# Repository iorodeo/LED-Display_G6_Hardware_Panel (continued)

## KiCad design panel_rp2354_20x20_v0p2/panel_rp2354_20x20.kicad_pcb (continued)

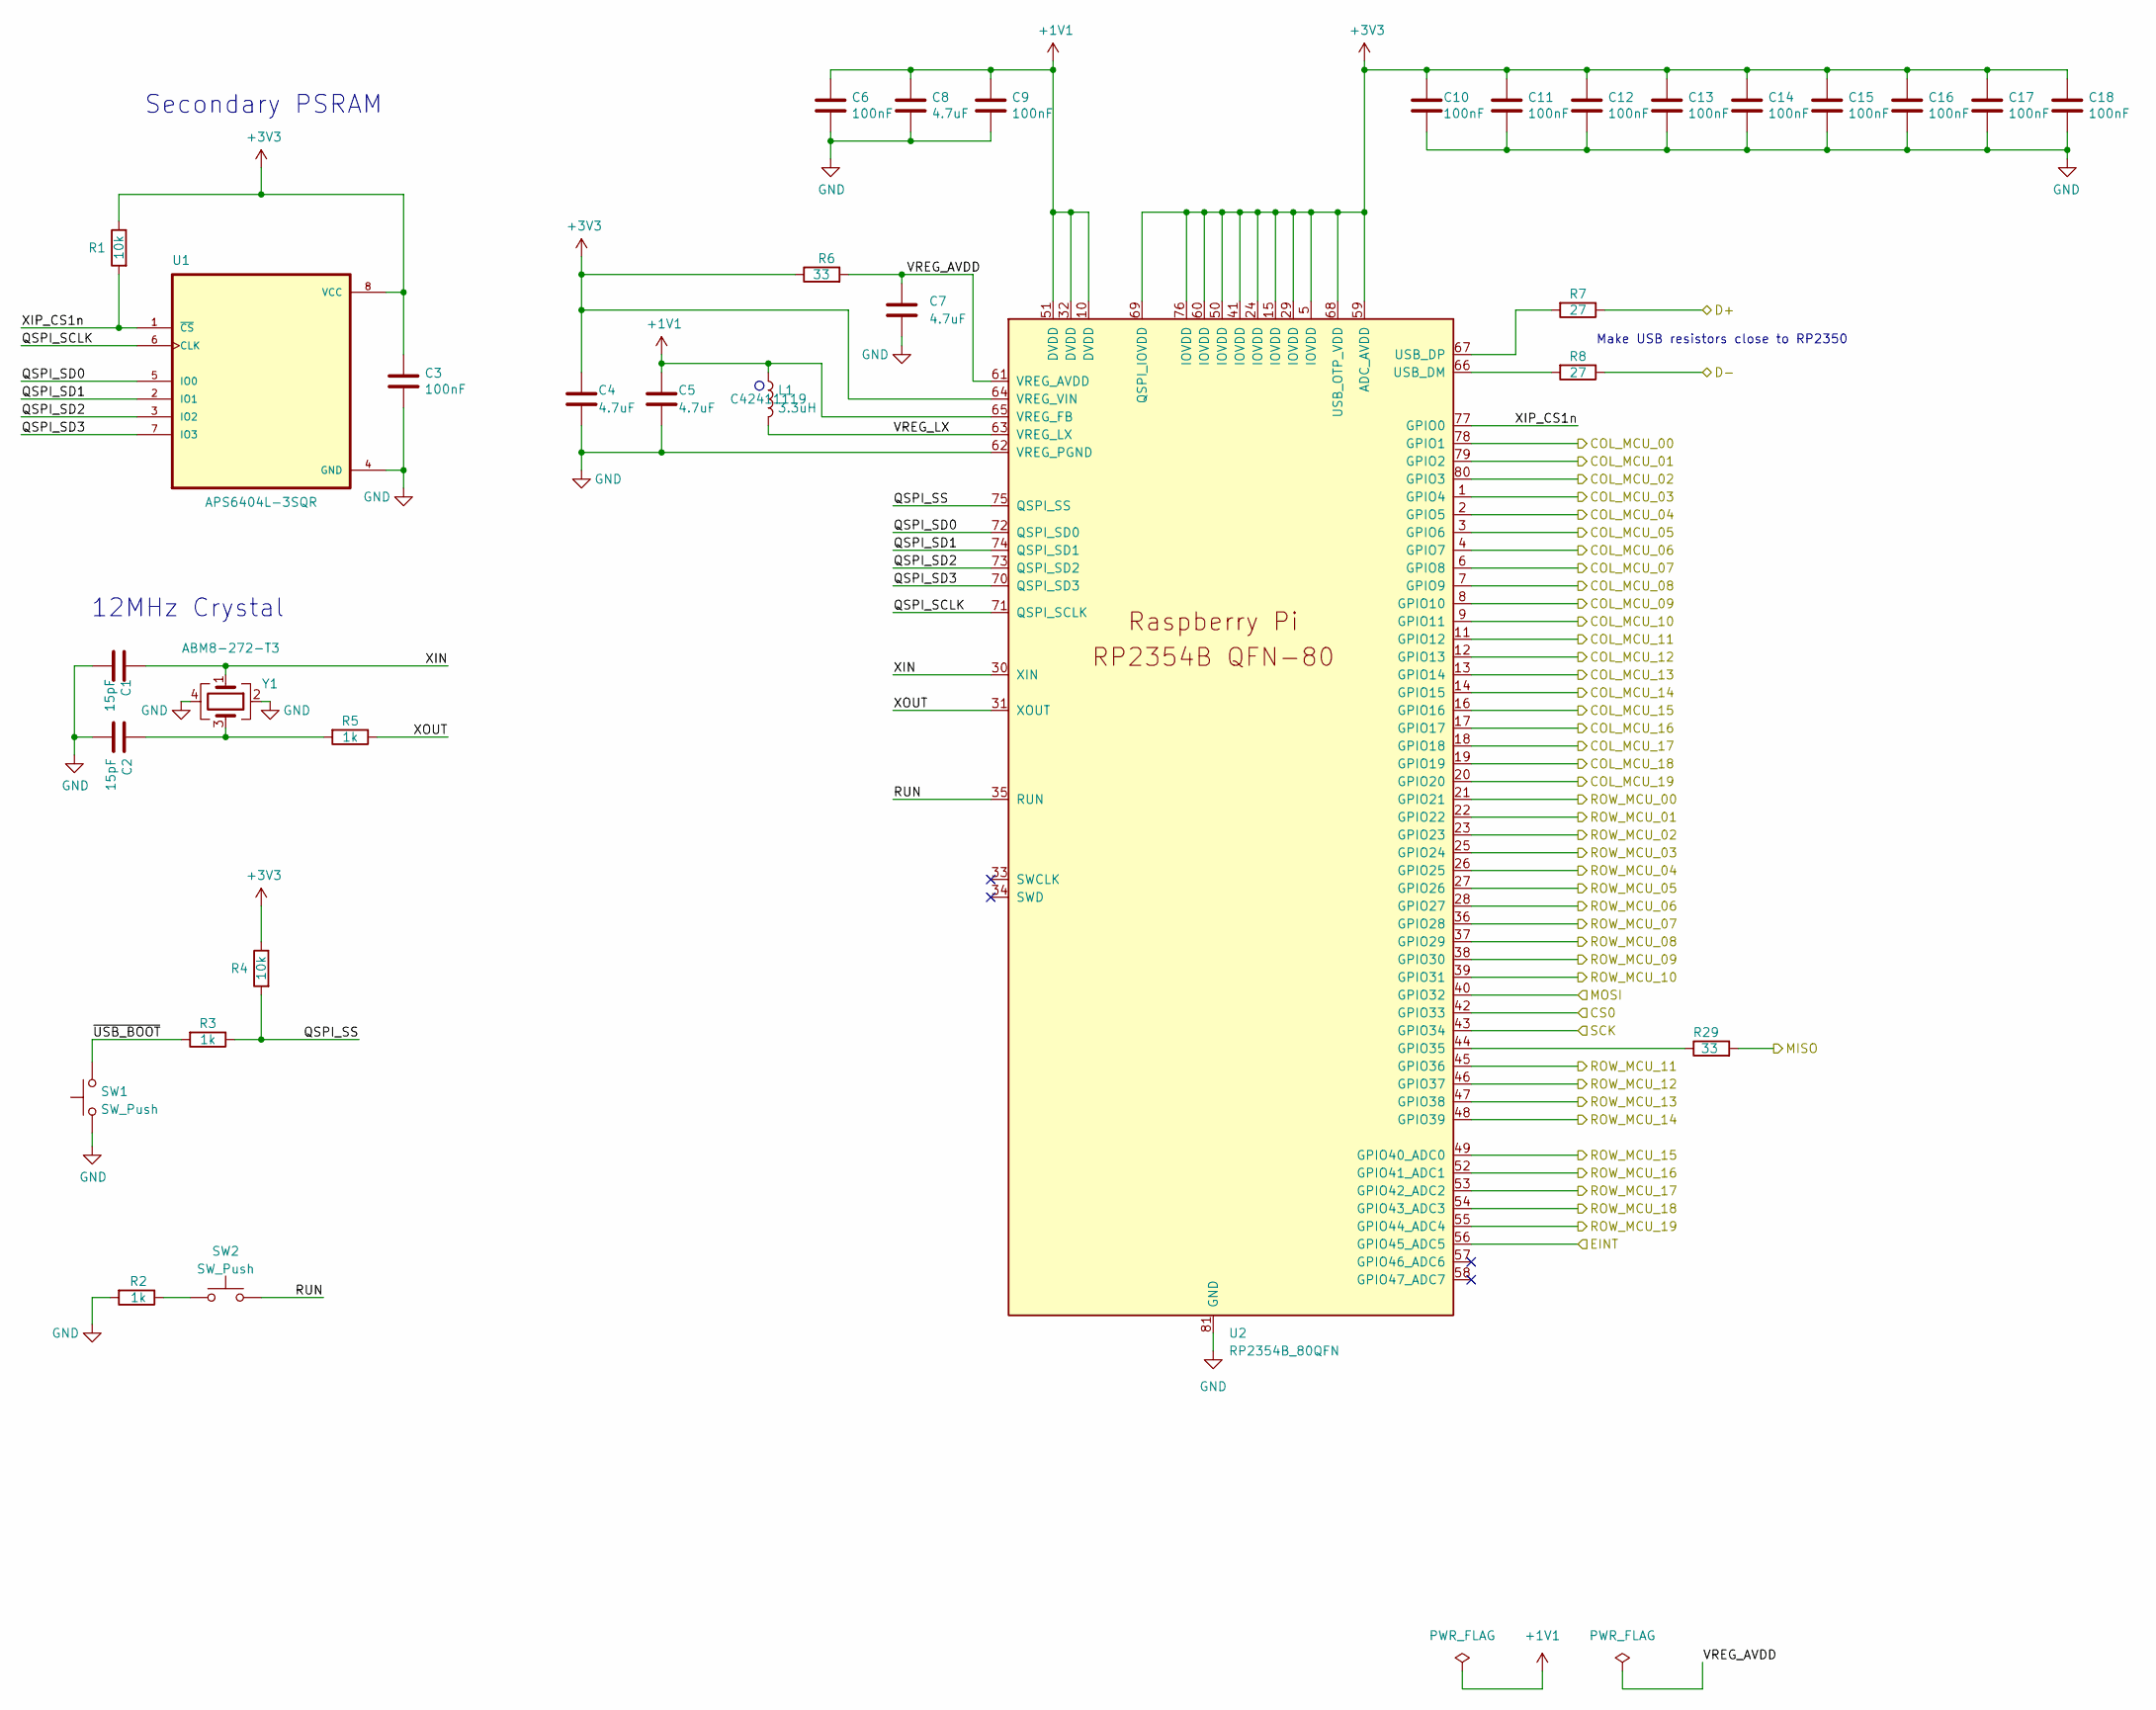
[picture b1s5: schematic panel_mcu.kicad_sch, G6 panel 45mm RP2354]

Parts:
C1, C2: 15pF; C_0201_0603Metric; LCSC Part # C541259
C3, C6, C9, C10, C11, C12, C13, C14, C15, C16, C17, C18: 100nF; C_0201_0603Metric; LCSC Part # C76939
C4, C5: 4.7uF; C_0402_1005Metric_small_pads; LCSC Part # C368809
C7, C8: 4.7uF; C_0402_1005Metric; LCSC Part # C368809
L1: 3.3uH; L_pol_2016; LCSC Part # C42411119
R1, R4: 10k; R_0201_0603Metric; LCSC Part # C473048
R2, R3, R5: 1k; R_0201_0603Metric; LCSC Part # C270365
R6, R29: 33; R_0201_0603Metric; LCSC Part # C295794
R7, R8: 27; R_0201_0603Metric; LCSC Part # C473051
SW1, SW2: SW_Push; TS-1088-AR02016; LCSC Part # C720477
U1: APS6404L-3SQR; flashmem_PSON50P300X200X60-9N; LCSC Part # C3040877
U2: RP2354B_80QFN; RP2350-QFN-80-1EP_10x10_P0.4mm_EP3.4x3.4mm_ThermalVias; LCSC Part # C39843328
Y1: ABM8-272-T3; Crystal_SMD_3225-4Pin_3.2x2.5mm; LCSC Part # C20625731

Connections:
+1V1: C5.1, C6.1, C8.1, C9.1, L1.1, U2.10 (DVDD), U2.32 (DVDD), U2.51 (DVDD), U2.65 (VREG_FB)
+3V3: C3.1, C4.1, C10.1, C11.1, C12.1, C13.1, C14.1, C15.1, C16.1, C17.1, C18.1, R1.1, R4.1, R6.1, U1.8 (VCC), U2.5 (IOVDD), U2.15 (IOVDD), U2.24 (IOVDD), U2.29 (IOVDD), U2.41 (IOVDD), U2.50 (IOVDD), U2.59 (ADC_AVDD), U2.60 (IOVDD), U2.64 (VREG_VIN), U2.68 (USB_OTP_VDD), U2.69 (QSPI_IOVDD), U2.76 (IOVDD); also elsewhere on the board
/drivers/COL_MCU_00: U2.78 (GPIO1); also elsewhere on the board
/drivers/COL_MCU_01: U2.79 (GPIO2); also elsewhere on the board
/drivers/COL_MCU_02: U2.80 (GPIO3); also elsewhere on the board
/drivers/COL_MCU_03: U2.1 (GPIO4); also elsewhere on the board
/drivers/COL_MCU_04: U2.2 (GPIO5); also elsewhere on the board
/drivers/COL_MCU_05: U2.3 (GPIO6); also elsewhere on the board
/drivers/COL_MCU_06: U2.4 (GPIO7); also elsewhere on the board
/drivers/COL_MCU_07: U2.6 (GPIO8); also elsewhere on the board
/drivers/COL_MCU_08: U2.7 (GPIO9); also elsewhere on the board
/drivers/COL_MCU_09: U2.8 (GPIO10); also elsewhere on the board
/drivers/COL_MCU_10: U2.9 (GPIO11); also elsewhere on the board
/drivers/COL_MCU_11: U2.11 (GPIO12); also elsewhere on the board
/drivers/COL_MCU_12: U2.12 (GPIO13); also elsewhere on the board
/drivers/COL_MCU_13: U2.13 (GPIO14); also elsewhere on the board
/drivers/COL_MCU_14: U2.14 (GPIO15); also elsewhere on the board
/drivers/COL_MCU_15: U2.16 (GPIO16); also elsewhere on the board
/drivers/COL_MCU_16: U2.17 (GPIO17); also elsewhere on the board
/drivers/COL_MCU_17: U2.18 (GPIO18); also elsewhere on the board
/drivers/COL_MCU_18: U2.19 (GPIO19); also elsewhere on the board
/drivers/COL_MCU_19: U2.20 (GPIO20); also elsewhere on the board
/drivers/ROW_MCU_00: U2.21 (GPIO21); also elsewhere on the board
/drivers/ROW_MCU_01: U2.22 (GPIO22); also elsewhere on the board
/drivers/ROW_MCU_02: U2.23 (GPIO23); also elsewhere on the board
/drivers/ROW_MCU_03: U2.25 (GPIO24); also elsewhere on the board
/drivers/ROW_MCU_04: U2.26 (GPIO25); also elsewhere on the board
/drivers/ROW_MCU_05: U2.27 (GPIO26); also elsewhere on the board
/drivers/ROW_MCU_06: U2.28 (GPIO27); also elsewhere on the board
/drivers/ROW_MCU_07: U2.36 (GPIO28); also elsewhere on the board
/drivers/ROW_MCU_08: U2.37 (GPIO29); also elsewhere on the board
/drivers/ROW_MCU_09: U2.38 (GPIO30); also elsewhere on the board
/drivers/ROW_MCU_10: U2.39 (GPIO31); also elsewhere on the board
/drivers/ROW_MCU_11: U2.45 (GPIO36); also elsewhere on the board
/drivers/ROW_MCU_12: U2.46 (GPIO37); also elsewhere on the board
/drivers/ROW_MCU_13: U2.47 (GPIO38); also elsewhere on the board
/drivers/ROW_MCU_14: U2.48 (GPIO39); also elsewhere on the board
/drivers/ROW_MCU_15: U2.49 (GPIO40_ADC0); also elsewhere on the board
/drivers/ROW_MCU_16: U2.52 (GPIO41_ADC1); also elsewhere on the board
/drivers/ROW_MCU_17: U2.53 (GPIO42_ADC2); also elsewhere on the board
/drivers/ROW_MCU_18: U2.54 (GPIO43_ADC3); also elsewhere on the board
/drivers/ROW_MCU_19: U2.55 (GPIO44_ADC4); also elsewhere on the board
/panel_header/CS0: U2.42 (GPIO33); also elsewhere on the board
/panel_header/EINT: U2.56 (GPIO45_ADC5); also elsewhere on the board
/panel_header/MISO: R29.2; also elsewhere on the board
/panel_header/MOSI: U2.40 (GPIO32); also elsewhere on the board
/panel_header/SCK: U2.43 (GPIO34); also elsewhere on the board
/panel_mcu/D+: R7.1; also elsewhere on the board
/panel_mcu/D-: R8.1; also elsewhere on the board
/panel_mcu/QSPI_SCLK: U1.6 (CLK), U2.71 (QSPI_SCLK)
/panel_mcu/QSPI_SD0: U1.5 (IO0), U2.72 (QSPI_SD0)
/panel_mcu/QSPI_SD1: U1.2 (IO1), U2.74 (QSPI_SD1)
/panel_mcu/QSPI_SD2: U1.3 (IO2), U2.73 (QSPI_SD2)
/panel_mcu/QSPI_SD3: U1.7 (IO3), U2.70 (QSPI_SD3)
/panel_mcu/QSPI_SS: R3.1, R4.2, U2.75 (QSPI_SS)
/panel_mcu/RUN: SW2.2, U2.35 (RUN)
/panel_mcu/VREG_AVDD: C7.1, R6.2, U2.61 (VREG_AVDD)
/panel_mcu/VREG_LX: L1.2, U2.63 (VREG_LX)
/panel_mcu/XIN: C1.1, U2.30 (XIN), Y1.1
/panel_mcu/XIP_CS1n: R1.2, U1.1 (~CS), U2.77 (GPIO0)
/panel_mcu/XOUT: R5.1, U2.31 (XOUT)
/panel_mcu/~USB_BOOT: R3.2, SW1.2
GND: C1.2, C2.2, C3.2, C4.2, C5.2, C6.2, C7.2, C8.2, C9.2, C10.2, C11.2, C12.2, C13.2, C14.2, C15.2, C16.2, C17.2, C18.2, R2.2, SW1.1, U1.4 (GND), U2.62 (VREG_PGND), U2.81 (GND), Y1.2, Y1.4; also elsewhere on the board
unnamed: C2.1, R5.2, Y1.3
unnamed: R2.1, SW2.1
unnamed: R29.1, U2.44 (GPIO35)
unnamed: R8.2, U2.66 (USB_DM)
unnamed: R7.2, U2.67 (USB_DP)

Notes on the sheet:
12MHz Crystal
Secondary PSRAM
Make USB resistors close to RP2350

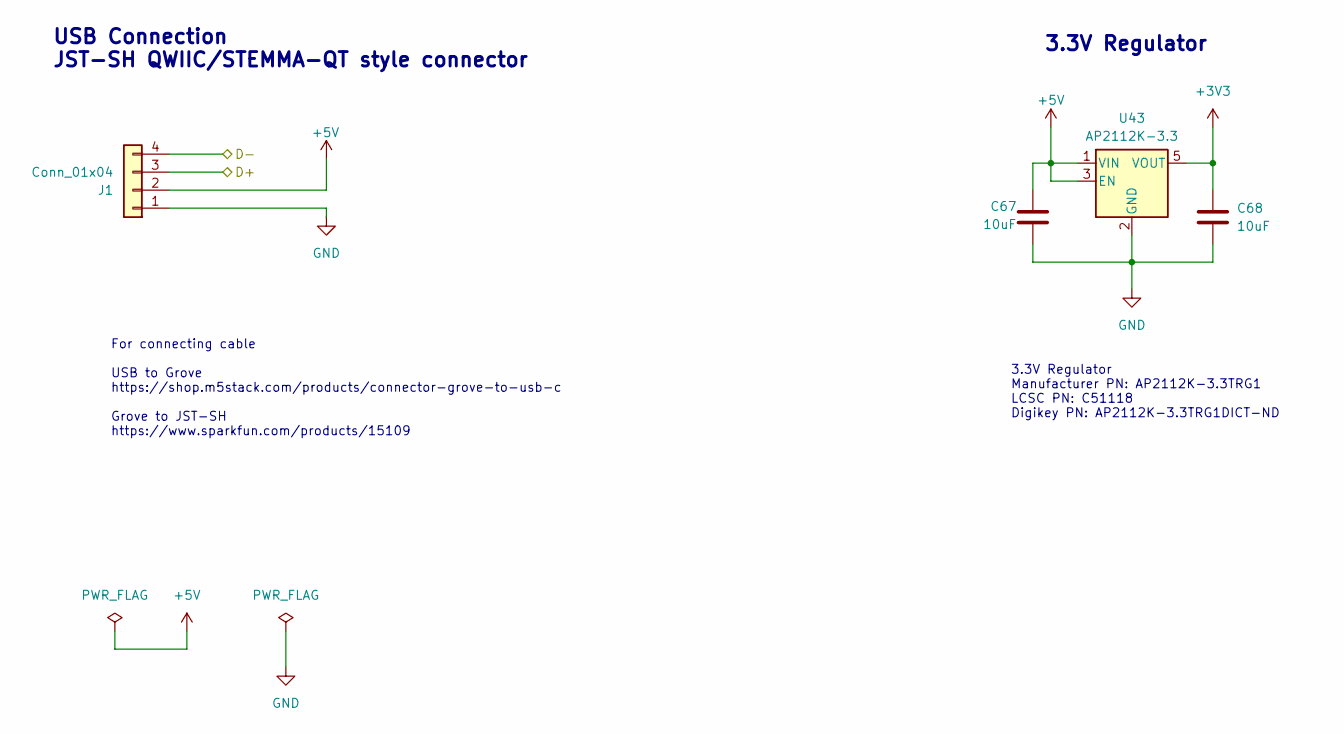
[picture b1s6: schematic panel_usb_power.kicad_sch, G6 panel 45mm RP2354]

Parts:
C67, C68: 10uF; C_0402_1005Metric; LCSC Part # C315248
J1: Conn_01x04; JST_SH_BM04B-SRSS-TB_1x04-1MP_P1.00mm_Vertical; LCSC Part # C160390
U43: AP2112K-3.3; SOT-23-5; LCSC Part # C51118

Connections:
+3V3: C68.1, U43.5 (VOUT); also elsewhere on the board
+5V: C67.1, J1.2, U43.1 (VIN), U43.3 (EN); also elsewhere on the board
/panel_mcu/D+: J1.3; also elsewhere on the board
/panel_mcu/D-: J1.4; also elsewhere on the board
GND: C67.2, C68.2, J1.1, U43.2 (GND); also elsewhere on the board

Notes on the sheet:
3.3V Regulator
For connecting cable USB to Grove https://shop.m5stack.com/products/connector-grove-to-usb-c Grove to JST-SH https://www.sparkfun.com/products/15109
USB Connection JST-SH QWIIC/STEMMA-QT style connector
3.3V Regulator Manufacturer PN: AP2112K-3.3TRG1 LCSC PN: C51118 Digikey PN: AP2112K-3.3TRG1DICT-ND

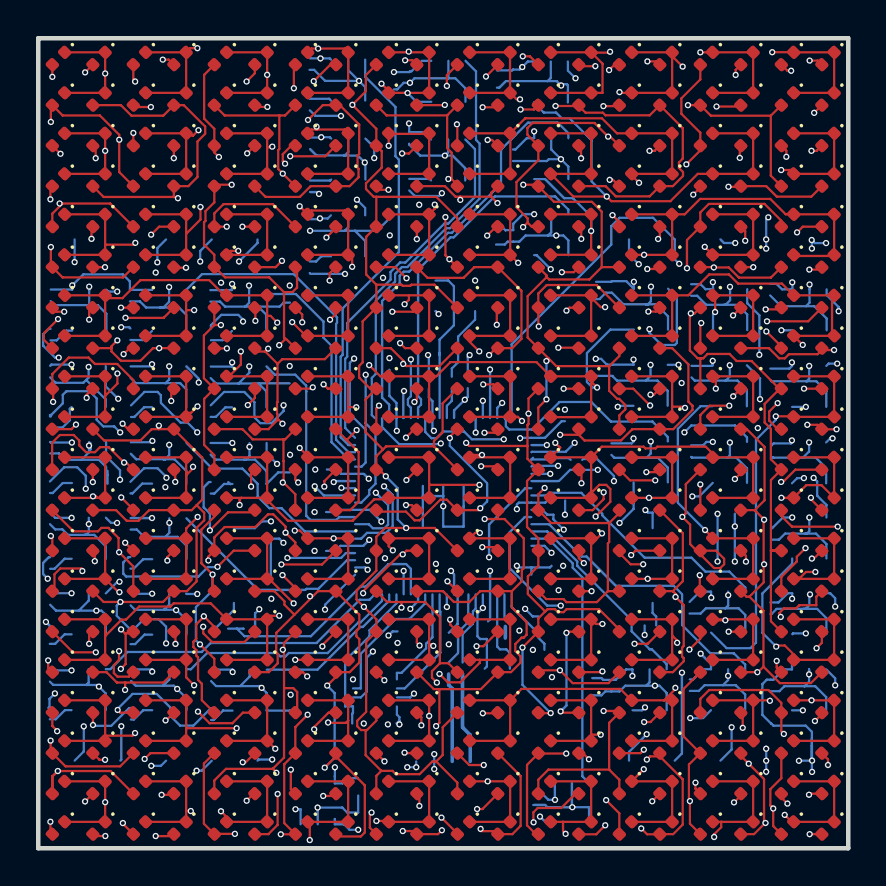
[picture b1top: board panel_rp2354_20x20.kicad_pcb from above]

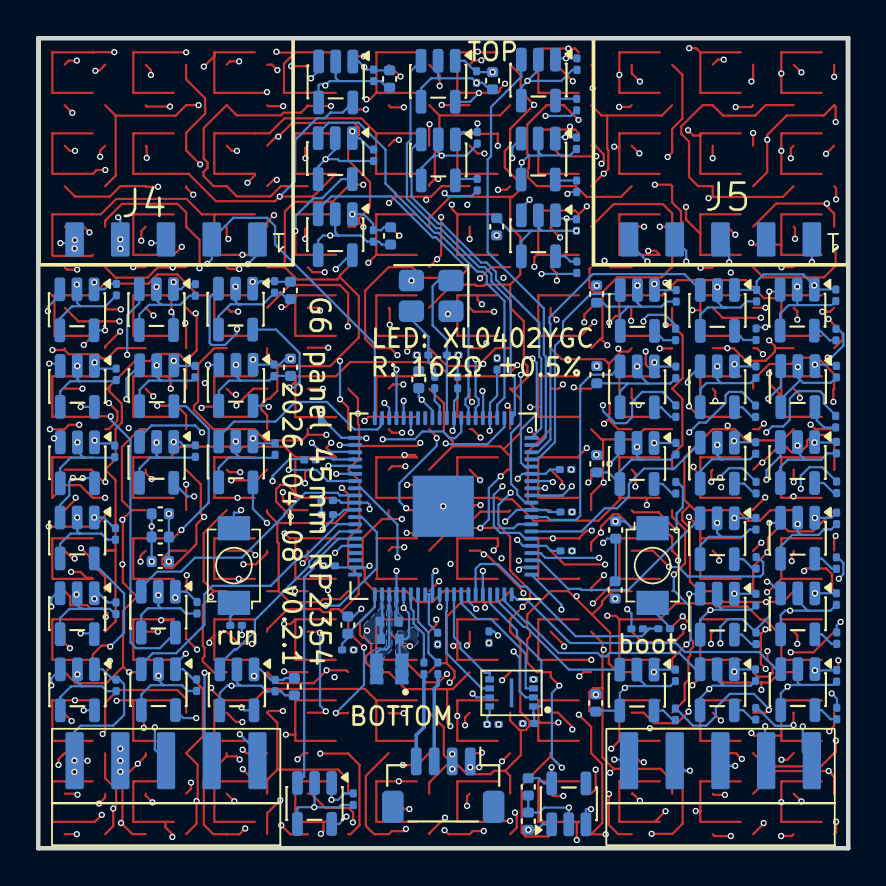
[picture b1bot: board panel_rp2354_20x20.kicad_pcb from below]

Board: 6 copper layers, 45.0 x 45.0 mm, 557 parts (157 on the bottom side), 132 nets.

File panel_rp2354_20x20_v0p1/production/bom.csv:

Designator,Footprint,Quantity,Value,LCSC Part #
"C1, C2",0201,2,15pF,C541259
"C10, C11, C12, C13, C14, C15, C16, C17, C18, C19, C20, C21, C22, C23, C24, C25, C26, C27, C28, C29, C3, C30, C31, C32, C33, C34, C35, C36, C37, C38, C39, C40, C41, C42, C43, C44, C45, C46, C47, C48, C49, C50, C51, C52, C53, C54, C55, C56, C57, C58, C6, C9",0201,52,100nF,C76939
"C4, C5, C7, C8",0402,4,4.7uF,C368809
"C59, C60, C61, C62, C63, C64, C65, C66, C67, C68, C69, C70, C71, C72, C73, C74, C75, C76",0402,18,10uF,C315248
"D1, D10, D100, D11, D12, D13, D14, D15, D16, D161, D162, D163, D164, D165, D166, D167, D168, D169, D17, D170, D171, D172, D173, D174, D175, D176, D177, D178, D179, D18, D180, D19, D2, D20, D241, D242, D243, D244, D245, D246, D247, D248, D249, D250, D251, D252, D253, D254, D255, D256, D257, D258, D259, D260, D3, D321, D322, D323, D324, D325, D326, D327, D328, D329, D330, D331, D332, D333, D334, D335, D336, D337, D338, D339, D340, D4, D5, D6, D7, D8, D81, D82, D83, D84, D85, D86, D87, D88, D89, D9, D90, D91, D92, D93, D94, D95, D96, D97, D98, D99",0402,100,LED_T0,C273601
"D101, D102, D103, D104, D105, D106, D107, D108, D109, D110, D111, D112, D113, D114, D115, D116, D117, D118, D119, D120, D181, D182, D183, D184, D185, D186, D187, D188, D189, D190, D191, D192, D193, D194, D195, D196, D197, D198, D199, D200, D21, D22, D23, D24, D25, D26, D261, D262, D263, D264, D265, D266, D267, D268, D269, D27, D270, D271, D272, D273, D274, D275, D276, D277, D278, D279, D28, D280, D29, D30, D31, D32, D33, D34, D341, D342, D343, D344, D345, D346, D347, D348, D349, D35, D350, D351, D352, D353, D354, D355, D356, D357, D358, D359, D36, D360, D37, D38, D39, D40",0402,100,LED_T1,C131223
"D121, D122, D123, D124, D125, D126, D127, D128, D129, D130, D131, D132, D133, D134, D135, D136, D137, D138, D139, D140, D201, D202, D203, D204, D205, D206, D207, D208, D209, D210, D211, D212, D213, D214, D215, D216, D217, D218, D219, D220, D281, D282, D283, D284, D285, D286, D287, D288, D289, D290, D291, D292, D293, D294, D295, D296, D297, D298, D299, D300, D361, D362, D363, D364, D365, D366, D367, D368, D369, D370, D371, D372, D373, D374, D375, D376, D377, D378, D379, D380, D41, D42, D43, D44, D45, D46, D47, D48, D49, D50, D51, D52, D53, D54, D55, D56, D57, D58, D59, D60",0402,100,LED_T2,C131223
"D141, D142, D143, D144, D145, D146, D147, D148, D149, D150, D151, D152, D153, D154, D155, D156, D157, D158, D159, D160, D221, D222, D223, D224, D225, D226, D227, D228, D229, D230, D231, D232, D233, D234, D235, D236, D237, D238, D239, D240, D301, D302, D303, D304, D305, D306, D307, D308, D309, D310, D311, D312, D313, D314, D315, D316, D317, D318, D319, D320, D381, D382, D383, D384, D385, D386, D387, D388, D389, D390, D391, D392, D393, D394, D395, D396, D397, D398, D399, D400, D61, D62, D63, D64, D65, D66, D67, D68, D69, D70, D71, D72, D73, D74, D75, D76, D77, D78, D79, D80",0402,100,LED_T3,C273601
J1,JST_SH_BM04B-SRSS-TB_1x04-1MP_P1.00mm_Vertical,1,Conn_01x04,C160390
"J4, J5",ConnRcpt_1x5_SMH-105-02-X-S,2,Conn_01x05,C21116902 
L1,L_pol_2016,1,3.3uH,C42411119
"R1, R4",0201,2,10k,C473048
"R10, R11, R14, R15, R18, R19, R22, R23, R26, R27",0201,10,165,C320715
"R12, R13, R16, R17, R20, R21, R24, R25, R28, R9",0201,10,270,C320799
"R2, R3, R5",0201,3,1k,C270365
R6,0201,1,33,C295794
"R7, R8",0201,2,27,C473051
"SW1, SW2",TS-1088-AR02016,2,SW_Push,C720477
U1,flashmem_PSON50P300X200X60-9N,1,APS6404L-3SQR,C3040877
"U10, U11, U12, U13, U14, U15, U16, U17, U18, U19, U20, U21, U22, U23, U24, U25, U26, U27, U28, U29, U3, U30, U31, U32, U33, U34, U35, U36, U37, U38, U39, U4, U40, U41, U42, U5, U6, U7, U8, U9",SOT-23-5,40,UCC27517,C99395
U2,RP2350-QFN-80-1EP_10x10_P0.4mm_EP3.4x3.4mm_ThermalVias,1,RP2354B_80QFN,C39843328
U43,SOT-23-5,1,AP2112K-3.3,C51118
Y1,Crystal_SMD_3225-4Pin_3.2x2.5mm,1,ABM8-272-T3,C20625731

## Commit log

2025-09-23 Renamed to panel_rp2354_20x20. Creaetd inition production files.
2025-09-24 Worked on rp2354 fabrication files.
2025-09-29 Fixed part rotation issues. Remove J2 J3 LCSC part as it was incorrect.
2025-09-29 Added some notes.
2025-09-30 Fixed net label issue ... changes CS3 to CS4.
2025-11-24 Minor changes ... to do with .step file creation.
2025-11-25 Move G6 rp2354 panel design to new repository.
2025-11-25 Added gate_driver spice simulation.
2025-11-25 Added simple led spice simulation.
2025-11-25 Increased panel border sligthly, added production archive.
    Increased the PCB border slightly (by 0.2mm on all sides) as some traces
    were too close to the edge. This was easier than move the traces as
    some are between the boundary and a component (typically an led).
    Added production archive for previous revisions of the design. Included
    JLCPCB PCB order details and PCBA info for helping with future orders.
2025-11-26 prepare v0.1.3
2026-04-08 order v0.2.0
    - connect EINT to pin 56
    - add R to MISO
    - change R for LED from 240 → 162
2026-04-09 shrink to 45x45
    - a few more vias, moved 2 capacitors by <1mm
    - moved text to silkscreen
2026-04-09 draft for v0.3.0
2026-04-09 fix XIP_CS1n pind
2026-04-10 cleanup
2026-04-10 fix conflict
2026-04-10 fix EINT note position
2026-04-27 initial documentation
